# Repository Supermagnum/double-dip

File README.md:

# double-dip
A small PCB that uses a TL082BCP chip with two op amps to amplify a signal from a contact microphone.

SMD adapter with LT6234 :
https://aisler.net/p/IXOHRKHO
https://github.com/Supermagnum/smd-adapter
It has lower self noise.

It has balanced output,input and runs on +48 phantom power. Shielded cable must be used for connection to the piezo crystals. Please use 0,5 W metal film resistors with 1% tolerance or better and audio quality capacitors.
C0G (NP0) or X7R capacitors is very good.

It is important that the circuit board is mounted inside a metal box, and Ø2mm conducting metal standoffs are used. The corner pads of the PCB board is reserved for that. Of course the PCB board and components must not come in contact with any metal surface expect the standoffs.

The circuit may benefit from a Zobel network, that is a 680 pF capacitor and a 150 ohms resistor in series between pin 2 and 3 on the output or the input connector. It should avoid high frequency oscillation in a long cable.

Why: The problem with piezo guitar pickups and piezoelectric crystals is that they are not well matched to typical audio inputs. By their nature they can generate a lot of signal, but they cannot drive a 50 kilohm typical line input. The pickup needs to work into a much higher impedance, typically 1 megohm or so.

So what to people do? They go and plug a piezoelectric disks output directly into the line input of their recorder, typical impedance 50k, or the plug-in-power mic input of their recorder, typical impedance about 7k, and they start to bitch and moan that this damn thing sounds tinny. Which is does ! But they don't understand why!

The reason why these devices often sound tinny is because the piezo sensor presents its signal through a series capacitance which is small, typically 15nF or less. When wired to a normal 50 kilohm line input this forms a high-pass filter, which eliminates the bass.

This circuit board solves that, and amplifies the signal. How many dB it amplifies is dependent on the resistance on the resistors used.The data for that is on the schematic diagram.

It's fairly easy and straight forward to solder the components to the circuit board, a nice pointy soldering iron, solder, a magnifying glass, and a ohm or multimeter is all that is needed. Of course one needs a suitable metal box, and the circuit boards components must not come in contact with the metal box. That will cause short circuit, so it's best mounted on stand offs. Also, use the magnifying glass to check that no one of the soldering pads has been bridged.

It can be used for a reverb plate, listening to the insides of a engine,recording the sound of vibrating things. You will need two piezoelectric disks for that, mounted in a metal box. Non electric conductive super glue is useable for that. Just glue them to a flat surface. The piezoelectric disks should be electrically insulated from the metal box.

Mechanics may even use it to discover trouble with bearings or other mechanisms not easily opened, but it will need a dedicated +48 volts phantom power supply with headphone jack for that specific usage.

Of course one can use a recorder like a tascam dr40x, as long as it can supply +48 volt phantom power, and has a headphone jack for monitoring.

A good set of headphones or ear protection with built in speakers will keep out unwanted sounds or noise.

Should also work nice with hydrophones. PZT-5H tubes is best for that. You want more gain, 35 or 40 dB for that. In case of a hydrophone it's possible to have the hydrophone attached with a long cable and the amplifier/buffer circuit close to the piezoelectric elements. It's of course extremely important that the circuit board and connections are absolutely waterproof. A epoxy filled container or inside the hydrophone bulb is OK. Commercial ones uses kerosene oil, so olive oil or sunflower oil is a great alternative as it will not pollute the environment if any leaks occurs.

Some interesting ideas can be found in: https://github.com/Supermagnum/piezo-balanced/blob/main/Barlow-et-al-2008-HydrophoneConstruction_TM-417.pdf 
Note: Ecopoxy Flowcast does not need any vacuum, just a mold and a way to hold the piezoelectric tubes centered. It's also safer to work with. Of course two piezoelectric disks inside something waterproof that can handle the water pressure is also useable. 

I used a simple metal box with thin walls that used to contain candy and filled it with food grade silicone.

The XLR 3 pin plug has a solder lug for the shield for a reason. Connect the shield and the drain wire to that spesific lug.
Those are wired up like this: https://github.com/Supermagnum/piezo-balanced/blob/main/XLR%2BConnector%2BPinout%2BDiagram%2BRear%2BPin%2B2%2BHot%2Bv2%2Bgreen__01.jpg

It is my opinion that a shielded cable with 3 conductors inside is the best. Suggested cable: Digi-Key Part Number: 30-00910-5-ND

Piezoelectric disk, red wire for positive polarity. Black for negative: https://github.com/Supermagnum/double-gain/blob/main/Piezo-element-6.jpg

Based on: http://www.richardmudhar.com/blog/piezo-contact-microphone-hi-z-amplifier-low-noise-version/

Some methods of mounting a piezoelectric disk can be found here: https://locusonus.org/wiki/index.php?page=Hydrophone.en

Top of PCB: https://github.com/Supermagnum/double-dip/blob/main/front.jpg

Top of pcb without components:https://github.com/Supermagnum/double-dip/blob/main/bare-front.jpg

Bottom of PCB: https://github.com/Supermagnum/double-dip/blob/main/back.jpg

Dimentions:
https://github.com/Supermagnum/double-dip/blob/main/dimentions.png

Schematic diagram: https://github.com/Supermagnum/double-dip/blob/main/tht-dip.pdf

Aisler: https://aisler.net/p/HVXYPXGN

Made with: http://www.kicad.org/

KiCad uses an integrated environment for all of the stages of the design process: Schematic capture, PCB layout, Gerber file generation/visualization, and library editing.

KiCad is a cross-platform program, and free!

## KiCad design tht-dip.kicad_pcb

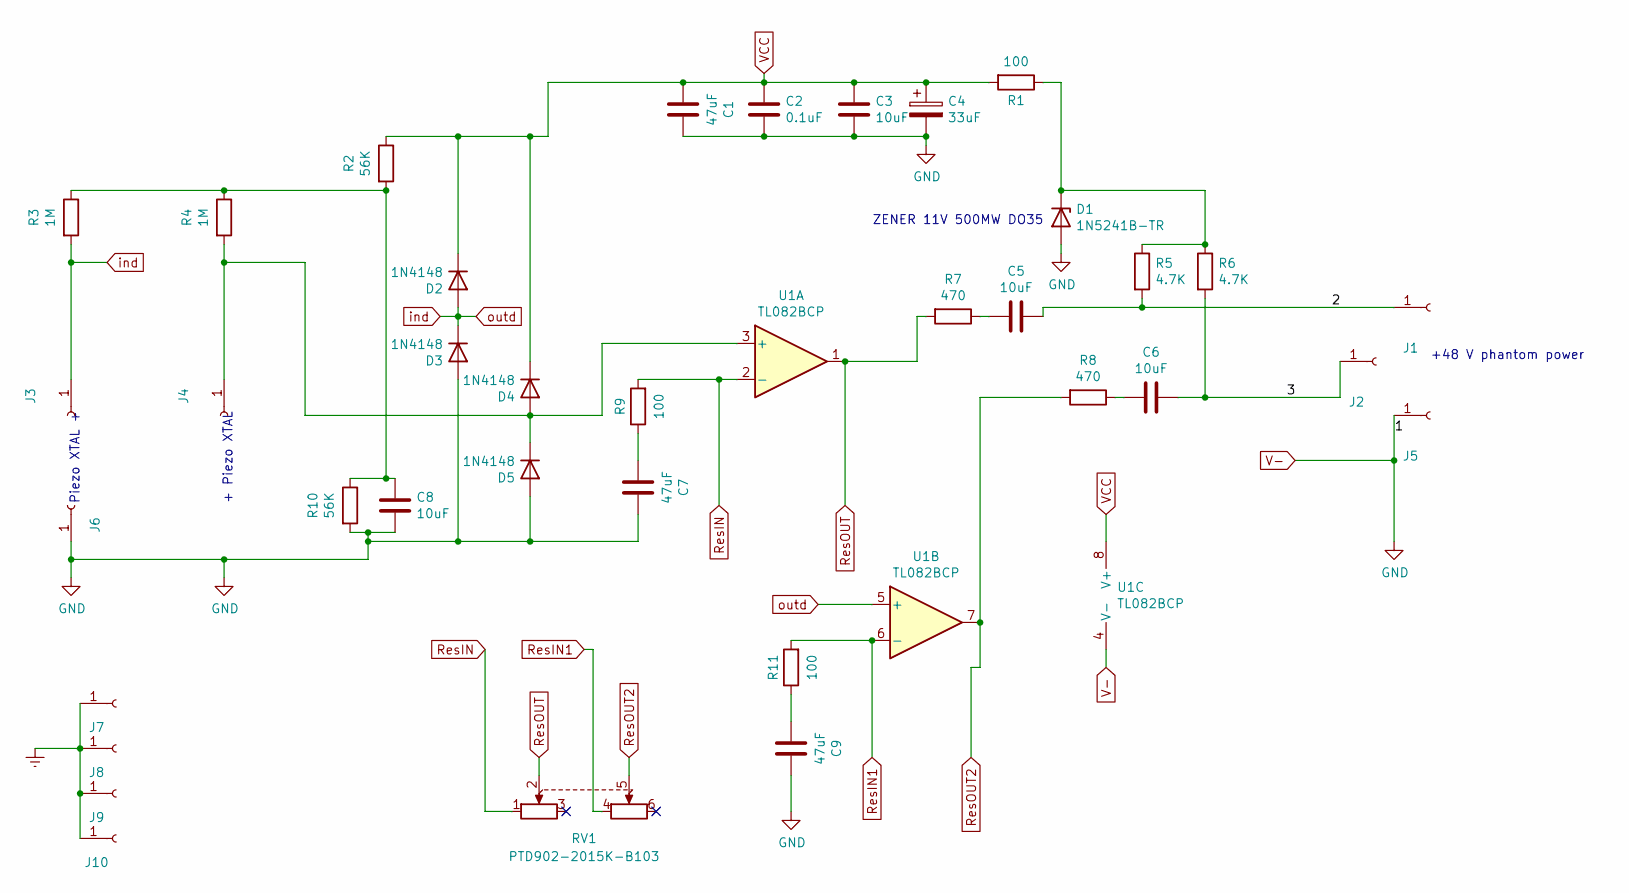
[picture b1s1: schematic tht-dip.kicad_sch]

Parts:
C1, C7, C9: 47uF; CP_Radial_D5.0mm_P2.00mm
C2: 0.1uF; C_Disc_D5.0mm_W2.5mm_P5.00mm
C3, C5, C6, C8: 10uF; C_Disc_D5.0mm_W2.5mm_P2.50mm
C4: 33uF; CP_Radial_D6.3mm_P2.50mm
D1: 1N5241B-TR; D_DO-35_SOD27_P7.62mm_Horizontal
D2, D3, D4, D5: 1N4148; D_DO-35_SOD27_P7.62mm_Horizontal
J1, J2, J3, J4, J5, J6, J7, J8, J9, J10: Conn_01x01_Female; MountingHole_2.2mm_M2_ISO7380_Pad
R1, R9, R11: 100; R_Axial_DIN0204_L3.6mm_D1.6mm_P5.08mm_Horizontal
R2, R10: 56K; R_Axial_DIN0204_L3.6mm_D1.6mm_P5.08mm_Horizontal
R3, R4: 1M; R_Axial_DIN0204_L3.6mm_D1.6mm_P5.08mm_Horizontal
R5, R6: 4.7K; R_Axial_DIN0204_L3.6mm_D1.6mm_P5.08mm_Horizontal
R7, R8: 470; R_Axial_DIN0204_L3.6mm_D1.6mm_P5.08mm_Horizontal
RV1: PTD902-2015K-B103
U1: TL082BCP; DIP-8_W7.62mm

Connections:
/2: C5.1, J1.1, R5.2
/3: C6.1, J2.1, R6.2
Earth: J7.1, J8.1, J9.1, J10.1
unnamed: C5.2, R7.1
unnamed: C6.2, R8.1
unnamed: C7.2, R9.1
unnamed: C8.1, R2.2, R3.1, R4.1, R10.1
unnamed: C9.2, R11.1
unnamed: D1.1 (K), R1.1, R5.1, R6.1
unnamed: D4.2 (A), D5.1 (K), J4.1, R4.2, U1.3 (+)
ResIN: R9.2, RV1.1, U1.2 (-)
ResIN1: R11.2, RV1.4, U1.6 (-)
ResOUT: R7.2, RV1.2, U1.1
ResOUT2: R8.2, RV1.5, U1.7
V-: C1.1, C2.2, C3.2, C4.2, C7.1, C8.2, C9.1, D1.2 (A), D3.2 (A), D5.2 (A), J5.1, J6.1, R10.2, U1.4 (V-)
VCC: C1.2, C2.1, C3.1, C4.1, D2.1 (K), D4.1 (K), R1.2, R2.1, U1.8 (V+)
ind: D2.2 (A), D3.1 (K), J3.1, R3.2, U1.5 (+)

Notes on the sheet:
ZENER 11V 500MW DO35
+ Piezo XTAL
Piezo XTAL +
+48 V phantom power

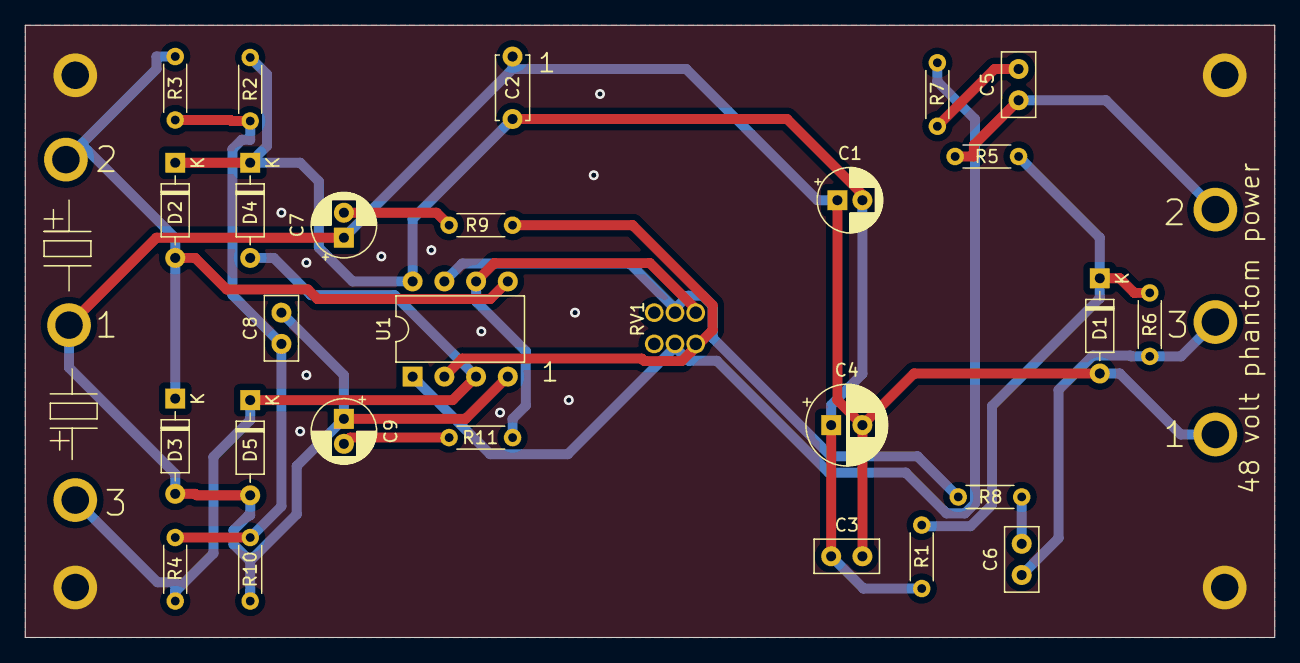
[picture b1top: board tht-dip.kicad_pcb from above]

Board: 2 copper layers, 100.0 x 49.0 mm, 37 parts (0 on the bottom side), 17 nets.

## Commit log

2021-07-04 Add files via upload
    updated files.
2021-07-16 Add files via upload
    Updated, with the addition of a 700 ohm resistor.
2021-07-17 Add files via upload
    Changed to TL082BCP , less current use.
